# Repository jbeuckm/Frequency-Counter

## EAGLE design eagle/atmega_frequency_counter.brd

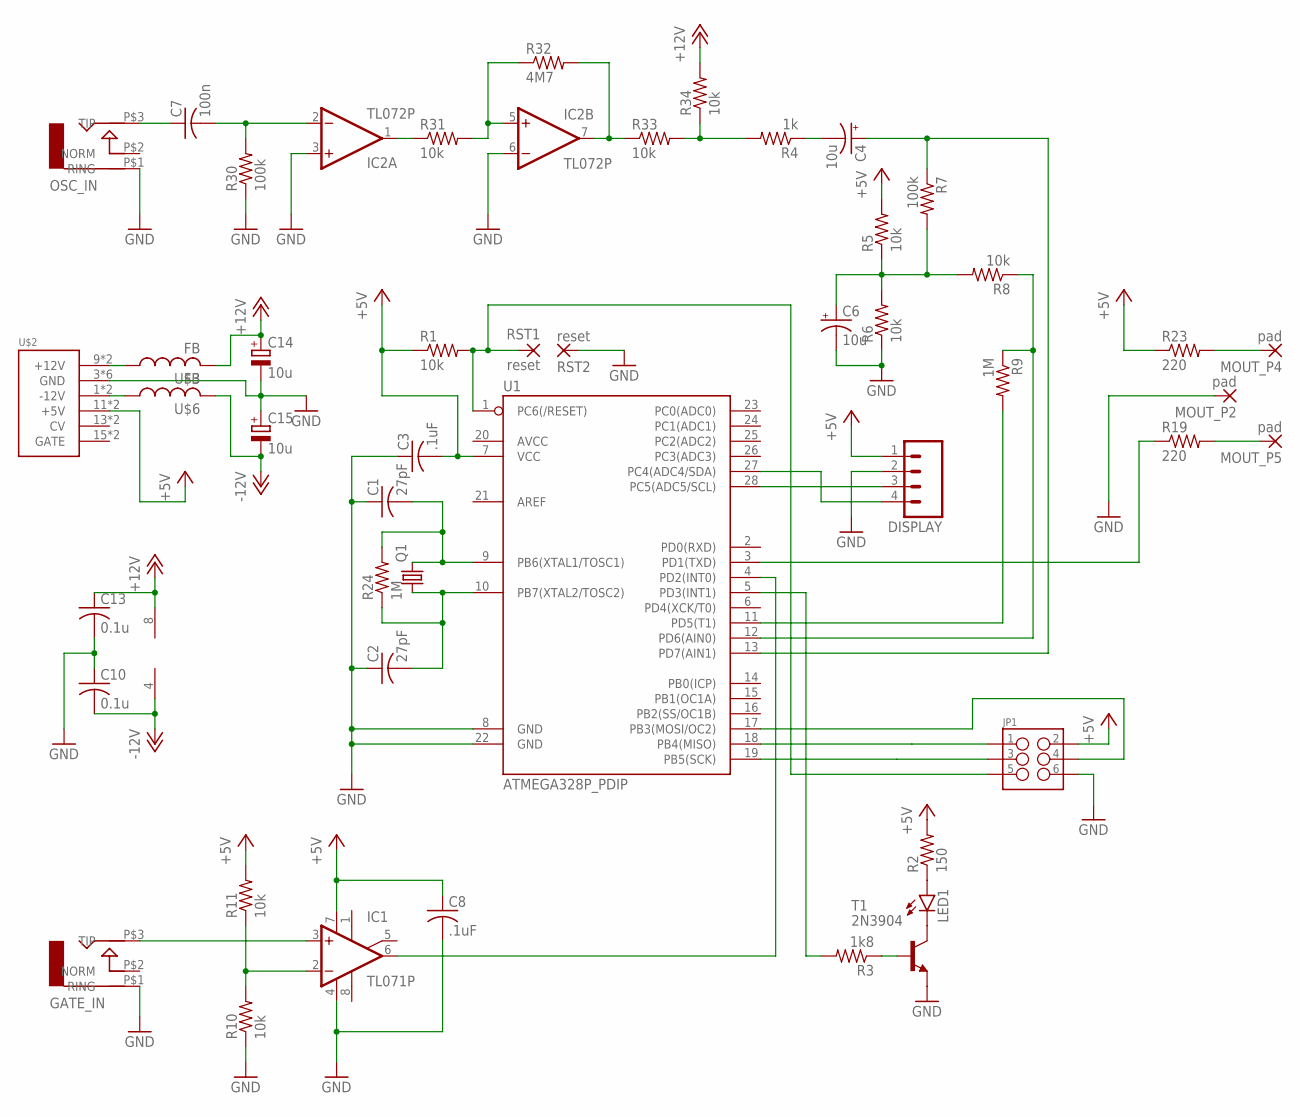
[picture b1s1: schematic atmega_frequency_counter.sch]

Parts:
C1, C2: 27pF; C025-040X050
C3, C8: .1uF; C050-024X044
C4, C6, C14, C15: 10u; B45181A
C7: 100n; C050-035X075
C10: 0.1u; C025-030X050
C13: 0.1u; C050-024X044
DISPLAY: M04POLAR; MOLEX-1X4
GATE_IN: AUDIO-JACK; ERTHENVAR-JACK-90DEG
IC1: TL071P; DIL08
IC2: TL072P; DIL08
JP1: M03X2NO_SILK; 2X3-NS
LED1: LED5MM
MOUT_P2, MOUT_P4, MOUT_P5: pad; 2,54/0,9
OSC_IN: AUDIO-JACK; ERTHENVAR-JACK-90DEG
Q1: CRYSTALHC49U70; HC49U70
R1, R5, R6, R8, R10, R11, R31, R33, R34: 10k; 0207/10
R2: 150; 0207/10
R3: 1k8; 0207/10
R4: 1k; 0207/10
R7, R30: 100k; 0207/10
R9, R24: 1M; 0207/10
R19, R23: 220; 0207/10
R32: 4M7; 0207/10
RST1, RST2: reset; 2,54/0,9
T1: 2N3904; TO92
U1: ATMEGA328P_PDIP; DIL28-3
U$2: POWER; POWER_16
U$3, U$6: FB

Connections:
+5V: C3.2, C8.1, DISPLAY.1, IC1.7 (V+), JP1.2, R1.1, R2.2, R5.2, R11.2, R23.1, U1.7 (VCC), U$2.11 (+5V), U$2.12 (+5V)
+12V: C13.1, C14.+, IC2.8 (V+), R34.2, U$3.P$2 (2)
-12V: C10.2, C15.-, IC2.4 (V-), U$6.P$2 (2)
GND: C1.1, C2.1, C3.1, C6.-, C8.2, C10.1, C13.2, C14.-, C15.+, DISPLAY.2, GATE_IN.P$1 (RING), IC1.4 (V-), IC2.3 (+IN), IC2.6 (-IN), JP1.6, MOUT_P2.1, OSC_IN.P$1 (RING), R6.1, R10.1, R30.1, RST2.1, T1.3 (E), U1.8 (GND), U1.22 (GND), U$2.3 (GND), U$2.4 (GND), U$2.5 (GND), U$2.6 (GND), U$2.7 (GND), U$2.8 (GND)
unnamed: LED1.K (C), T1.1 (C)
unnamed: DISPLAY.3, U1.28 (PC5(ADC5/SCL))
unnamed: DISPLAY.4, U1.27 (PC4(ADC4/SDA))
unnamed: C1.2, Q1.2, R24.2, U1.9 (PB6(XTAL1/TOSC1))
unnamed: C2.2, Q1.1, R24.1, U1.10 (PB7(XTAL2/TOSC2))
unnamed: R3.1, T1.2 (B)
unnamed: R3.2, U1.5 (PD3(INT1))
unnamed: LED1.A, R2.1
unnamed: C4.-, R4.1
unnamed: JP1.3, U1.19 (PB5(SCK))
unnamed: C4.+, R7.1, U1.13 (PD7(AIN1))
unnamed: C6.+, R5.1, R6.2, R7.2, R8.2
unnamed: IC1.2 (-IN), R10.2, R11.1
unnamed: R8.1, R9.1, U1.12 (PD6(AIN0))
unnamed: R9.2, U1.11 (PD5(T1))
unnamed: GATE_IN.P$3 (TIP), IC1.3 (+IN)
unnamed: IC1.6 (OUT), U1.4 (PD2(INT0))
unnamed: JP1.4, U1.17 (PB3(MOSI/OC2))
unnamed: U$2.9 (+12V), U$2.10 (+12V), U$3.P$1 (1)
unnamed: U$2.1 (-12V), U$2.2 (-12V), U$6.P$1 (1)
unnamed: JP1.5, R1.2, RST1.1, U1.1 (PC6(/RESET))
unnamed: JP1.1, U1.18 (PB4(MISO))
unnamed: MOUT_P5.1, R19.2
unnamed: MOUT_P4.1, R23.2
unnamed: C7.1, OSC_IN.P$3 (TIP)
unnamed: R19.1, U1.3 (PD1(TXD))
unnamed: C7.2, IC2.2 (-IN), R30.2
unnamed: IC2.1 (OUT), R31.1
unnamed: IC2.5 (+IN), R31.2, R32.1
unnamed: IC2.7 (OUT), R32.2, R33.1
unnamed: R4.2, R33.2, R34.1

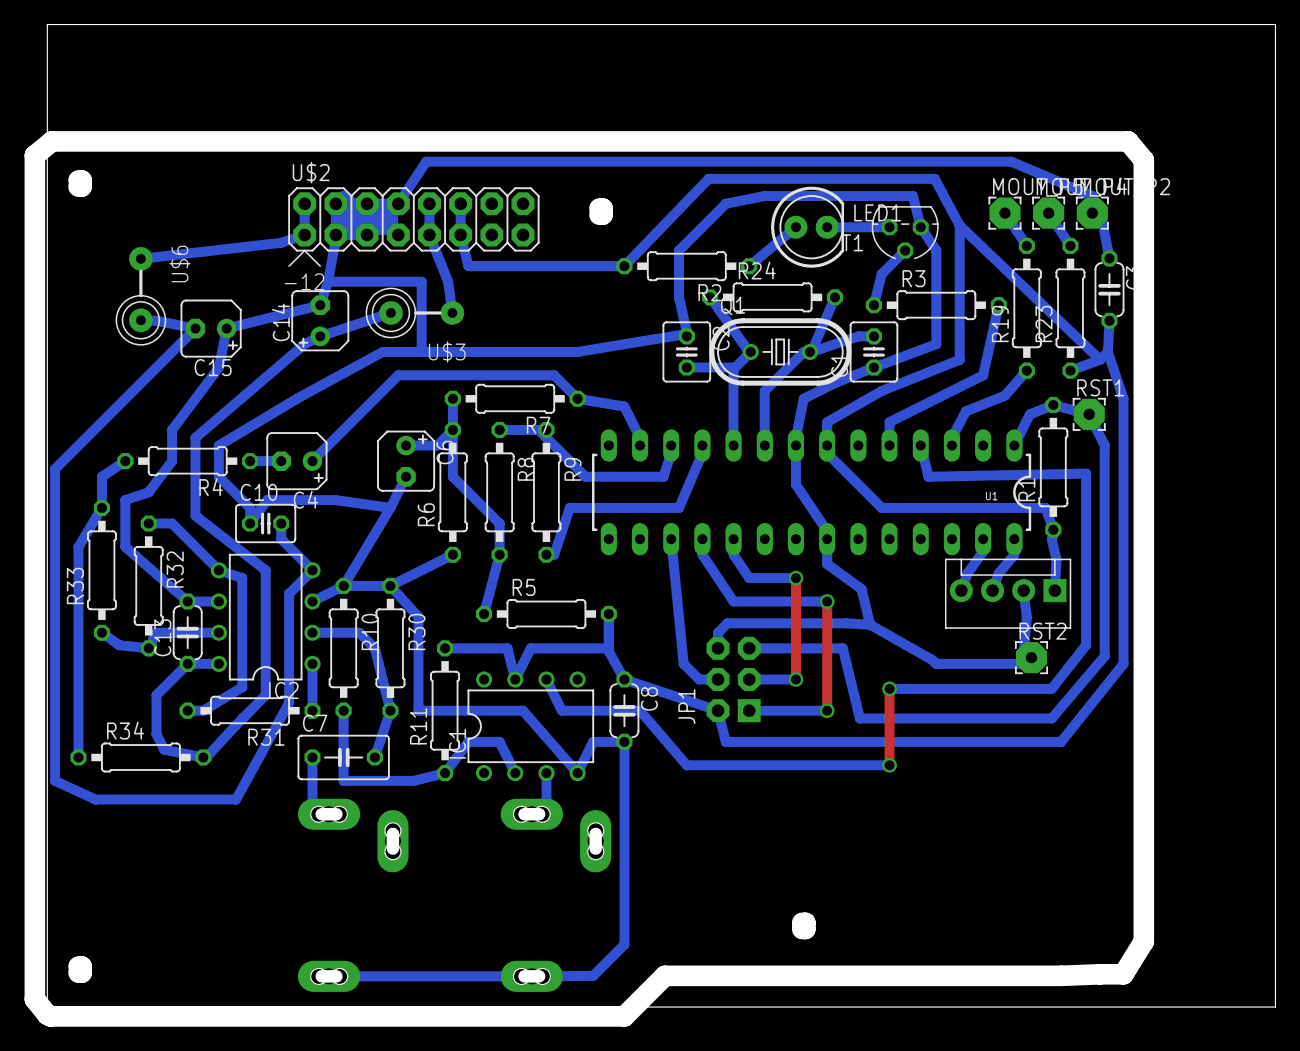
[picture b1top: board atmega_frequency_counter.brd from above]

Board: 2 copper layers, 100.2 x 79.9 mm, 48 parts (0 on the bottom side), 35 nets.

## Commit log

2016-01-06 layout
2016-01-06 gcode
2016-01-09 tweaked
2016-01-29 panel and display inverted for panel orientation
2017-09-23 redistributing freq period library

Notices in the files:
parts and their libraries:
SparkFun-Connectors: Licensing: Creative Commons ShareAlike 4.0 International - https://creativecommons.org/licenses/by-sa/4.0
